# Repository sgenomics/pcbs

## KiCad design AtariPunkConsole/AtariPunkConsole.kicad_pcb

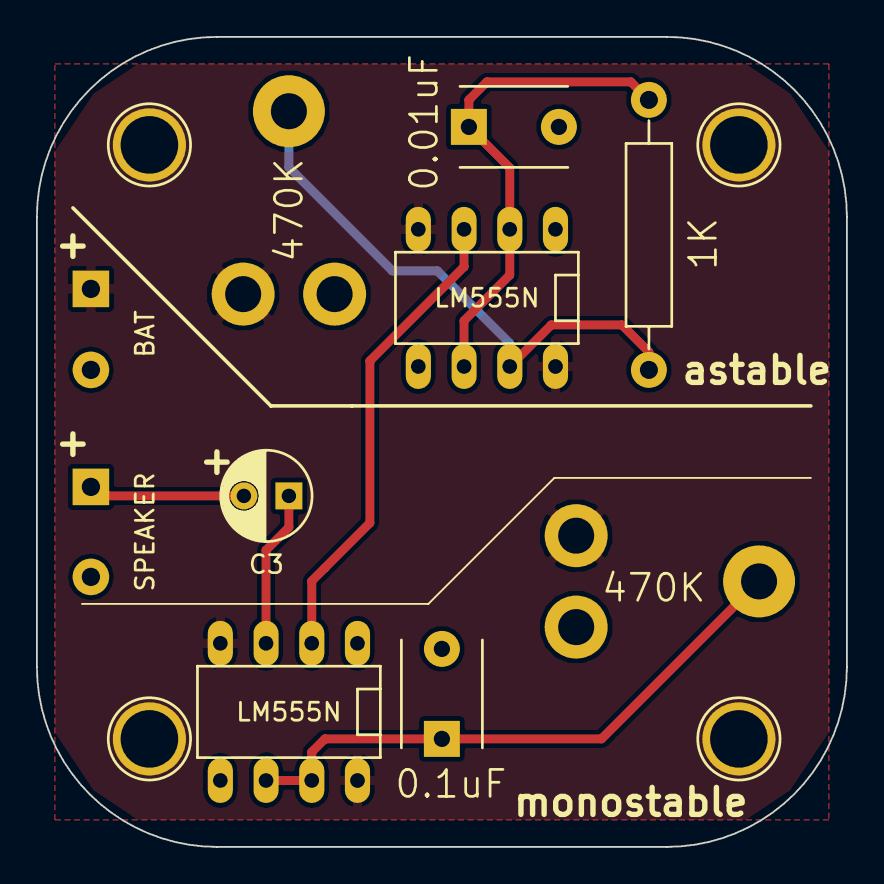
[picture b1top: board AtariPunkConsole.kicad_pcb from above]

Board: 2 copper layers, 45.0 x 45.0 mm, 10 parts (0 on the bottom side), 8 nets.

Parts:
C1: 0.01uF; C_Disc_D6_P5
C2: 0.1uF; C_Disc_D6_P5
C3: 10uF; C_Radial_D5_L11_P2.5
P1: SPEAKER; Socket_Strip_Straight_1x02
P2: BAT; Socket_Strip_Straight_1x02
R1: 1K; Resistor_Horizontal_RM15mm
U1, U2: LM555N; DIP-8__300
VR1, VR2: 470K; PNZ10Z

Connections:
+9V: P2.1, U1.4, U1.8, U2.4, U2.8, VR1.1, VR2.1
GND: C1.2, C2.2, P1.2, P2.2, U1.1, U2.1
unnamed: C1.1, R1.2, U1.2, U1.6
unnamed: C2.1, U2.6, U2.7, VR2.2
unnamed: C3.1, U2.3
unnamed: C3.2, P1.1
unnamed: R1.1, U1.7, VR1.2
unnamed: U1.3, U2.2

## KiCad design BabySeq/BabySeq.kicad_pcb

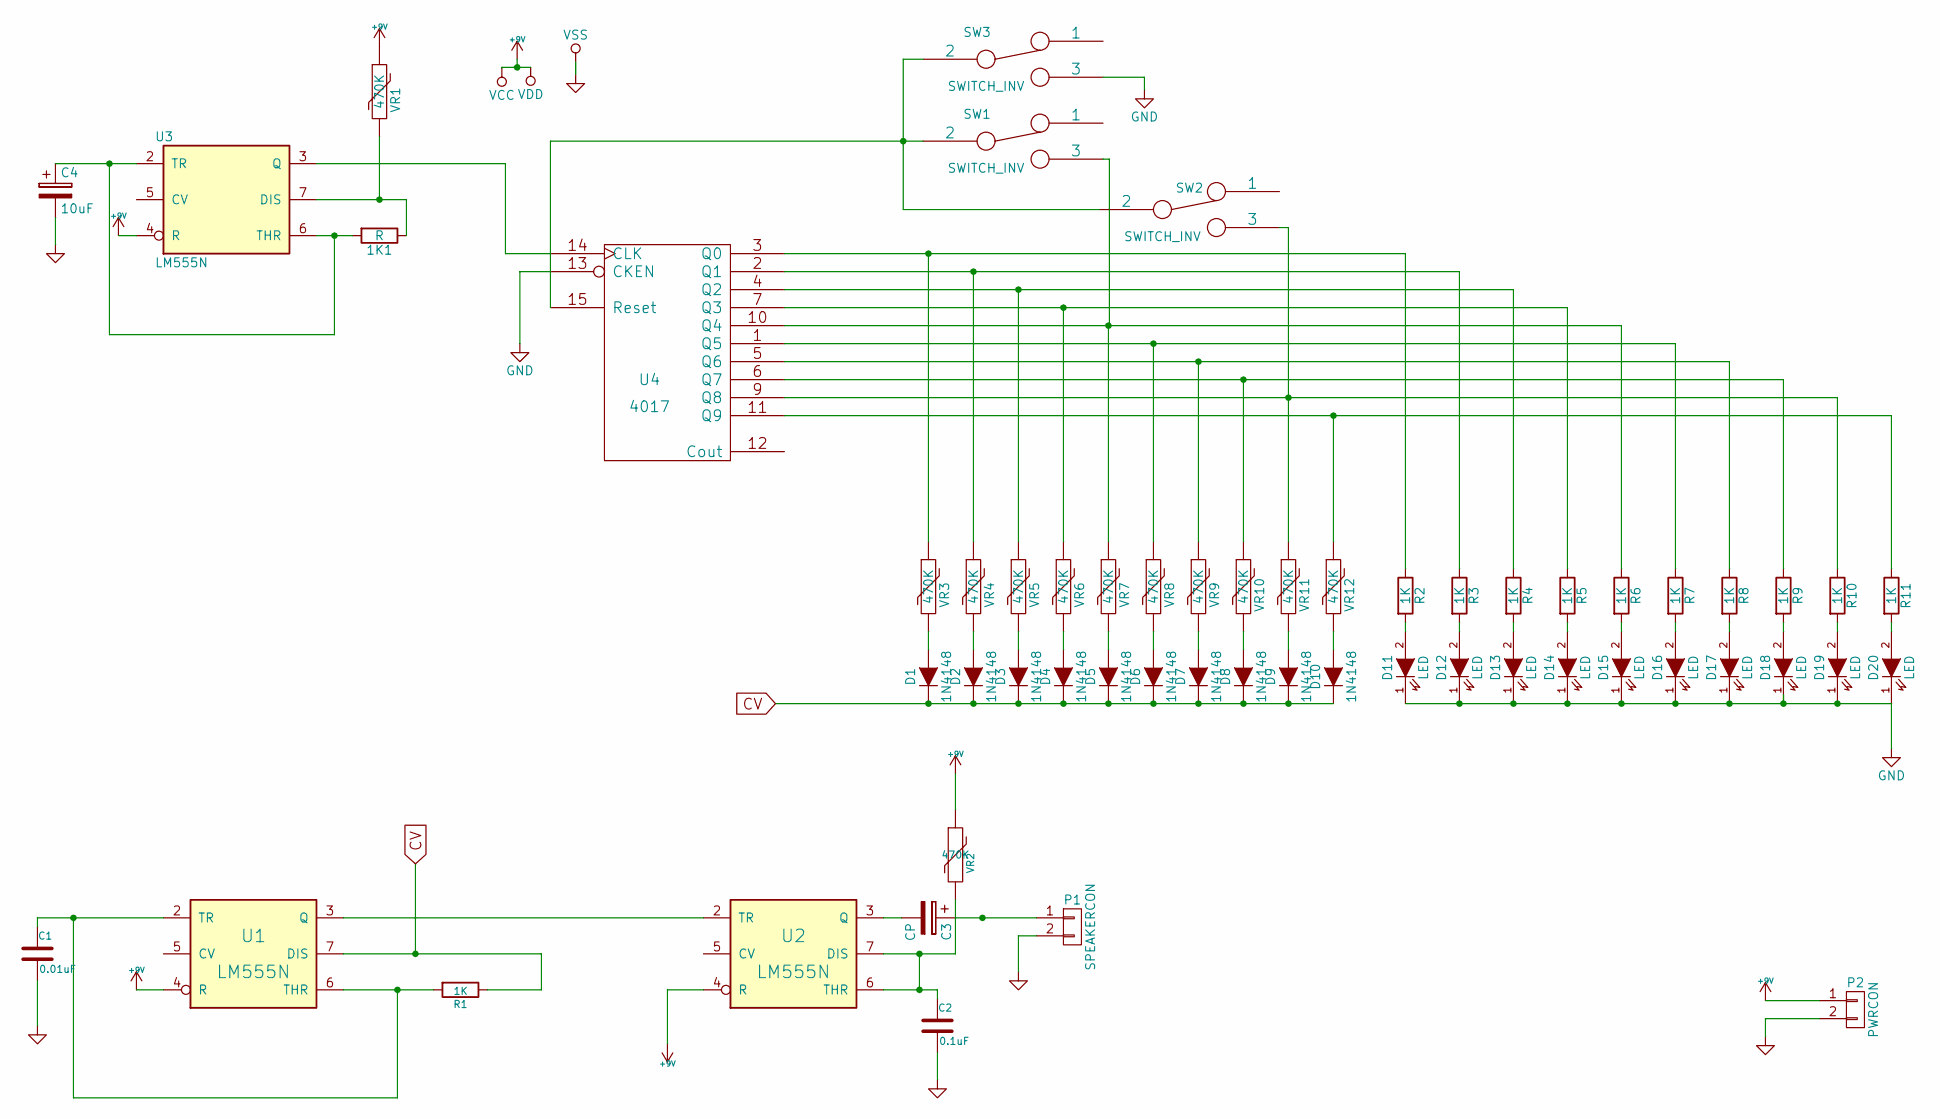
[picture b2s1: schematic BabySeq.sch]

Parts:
1K1: R; Resistor_Horizontal_RM15mm
C1: 0.01uF; C_Disc_D6_P5
C2: 0.1uF; C_Disc_D6_P5
C3: CP; C_Radial_D5_L11_P2.5
C4: 10uF; C_Radial_D5_L11_P2.5
D1, D2, D3, D4, D5, D6, D7, D8, D9, D10: 1N4148; Diode_DO-35_SOD27_Horizontal_RM10
D11, D12, D13, D14, D15, D16, D17, D18, D19, D20: LED; LED-5MM
P1: SPEAKERCON; Socket_Strip_Straight_1x02
P2: PWRCON; Socket_Strip_Straight_1x02
R1, R2, R3, R4, R5, R6, R7, R8, R9, R10, R11: 1K; Resistor_Horizontal_RM10mm
SW1, SW2, SW3: SWITCH_INV; CK_FARN1201430
U1, U2, U3: LM555N; DIP-8_W7.62mm_LongPads
U4: 4017; DIP-16_W7.62mm_LongPads
VR1, VR2, VR3, VR4, VR5, VR6, VR7, VR8, VR9, VR10, VR11, VR12: 470K; PNZ10Z

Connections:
+9V: P2.1, U1.4 (R), U1.8 (VCC), U2.4 (R), U2.8 (VCC), U3.4 (R), U3.8 (VCC), U4.16 (VDD), VR1.1, VR2.1
CV: D1.1 (K), D2.1 (K), D3.1 (K), D4.1 (K), D5.1 (K), D6.1 (K), D7.1 (K), D8.1 (K), D9.1 (K), D10.1 (K), R1.1, U1.7 (DIS)
GND: C1.2, C2.2, C4.2, D11.1 (K), D12.1 (K), D13.1 (K), D14.1 (K), D15.1 (K), D16.1 (K), D17.1 (K), D18.1 (K), D19.1 (K), D20.1 (K), P1.2, P2.2, SW3.3, U1.1 (GND), U2.1 (GND), U3.1 (GND), U4.8 (VSS), U4.13 (CKEN)
unnamed: 1K1.1, U3.7 (DIS), VR1.2
unnamed: 1K1.2, C4.1, U3.2 (TR), U3.6 (THR)
unnamed: C1.1, R1.2, U1.2 (TR), U1.6 (THR)
unnamed: C2.1, U2.6 (THR), U2.7 (DIS), VR2.2
unnamed: C3.1, P1.1
unnamed: C3.2, U2.3 (Q)
unnamed: D1.2 (A), VR3.2
unnamed: D2.2 (A), VR4.2
unnamed: D3.2 (A), VR5.2
unnamed: D4.2 (A), VR6.2
unnamed: D5.2 (A), VR7.2
unnamed: D6.2 (A), VR8.2
unnamed: D7.2 (A), VR9.2
unnamed: D8.2 (A), VR10.2
unnamed: D9.2 (A), VR11.2
unnamed: D10.2 (A), VR12.2
unnamed: D11.2 (A), R2.2
unnamed: D12.2 (A), R3.2
unnamed: D13.2 (A), R4.2
unnamed: D14.2 (A), R5.2
unnamed: D15.2 (A), R6.2
unnamed: D16.2 (A), R7.2
unnamed: D17.2 (A), R8.2
unnamed: D18.2 (A), R9.2
unnamed: D19.2 (A), R10.2
unnamed: D20.2 (A), R11.2
unnamed: R2.1, U4.3 (Q0), VR3.1
unnamed: R3.1, U4.2 (Q1), VR4.1
unnamed: R4.1, U4.4 (Q2), VR5.1
unnamed: R5.1, U4.7 (Q3), VR6.1
unnamed: R6.1, SW1.3, U4.10 (Q4), VR7.1
unnamed: R7.1, U4.1 (Q5), VR8.1
unnamed: R8.1, U4.5 (Q6), VR9.1
unnamed: R9.1, U4.6 (Q7), VR10.1
unnamed: R10.1, SW2.3, U4.9 (Q8), VR11.1
unnamed: R11.1, U4.11 (Q9), VR12.1
unnamed: SW1.2, SW2.2, SW3.2, U4.15 (Reset)
unnamed: U1.3 (Q), U2.2 (TR)
unnamed: U3.3 (Q), U4.14 (CLK)

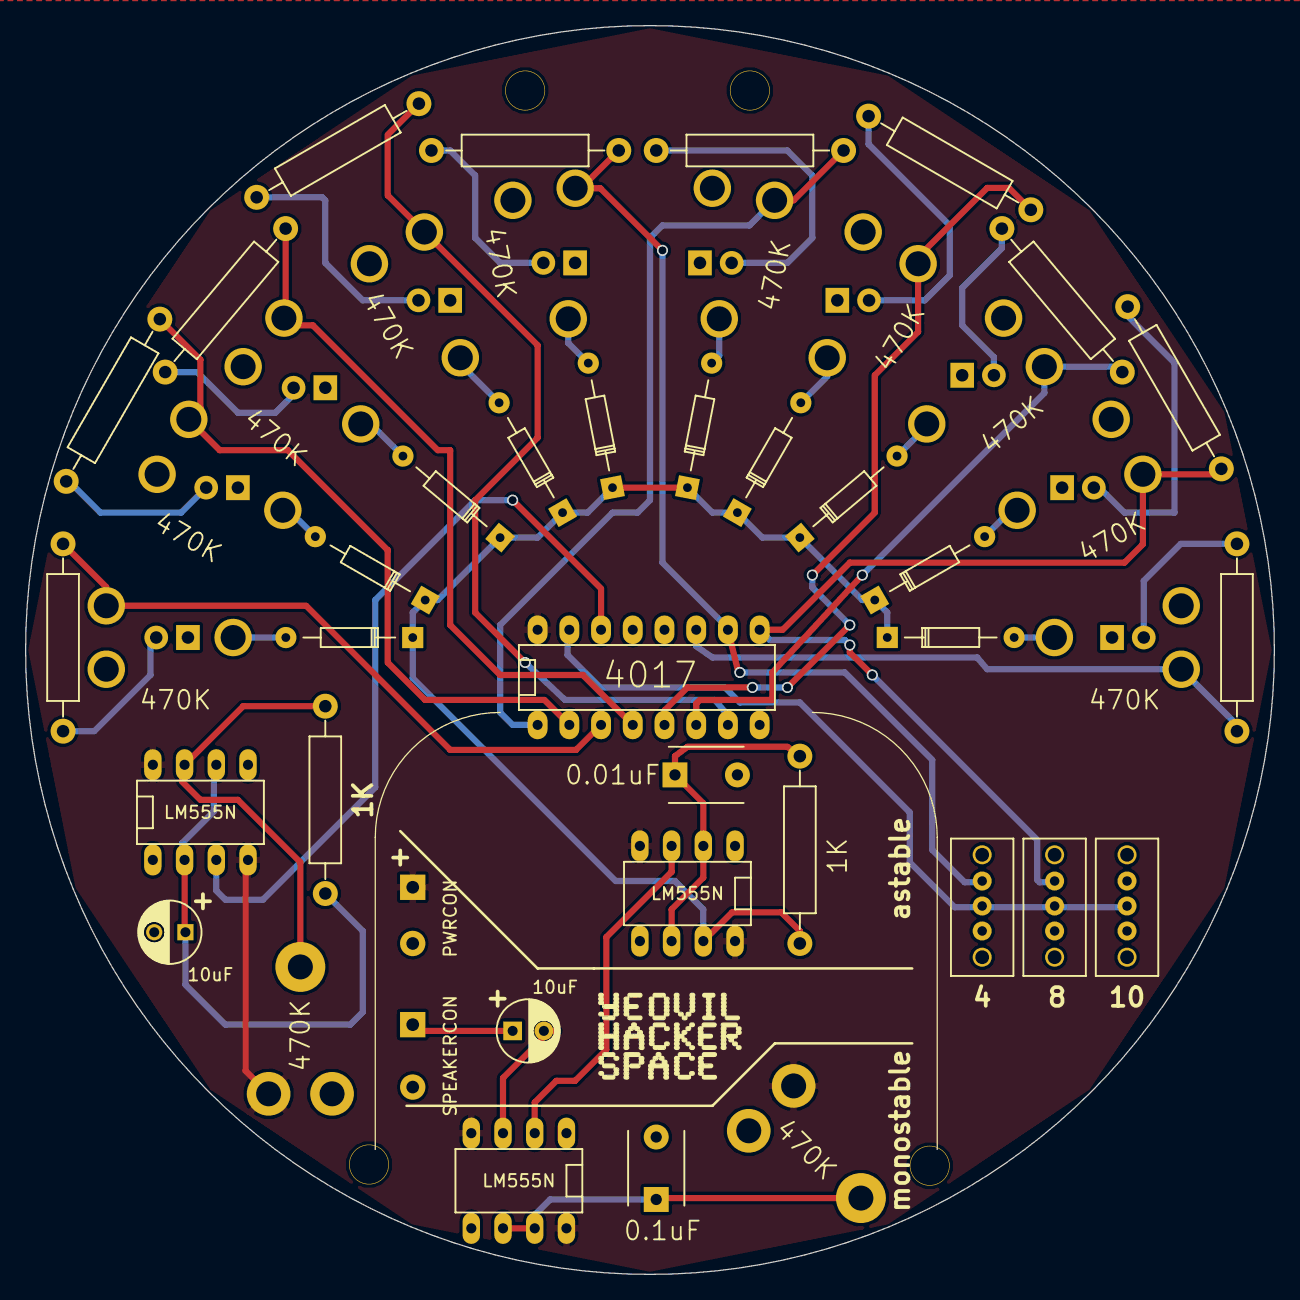
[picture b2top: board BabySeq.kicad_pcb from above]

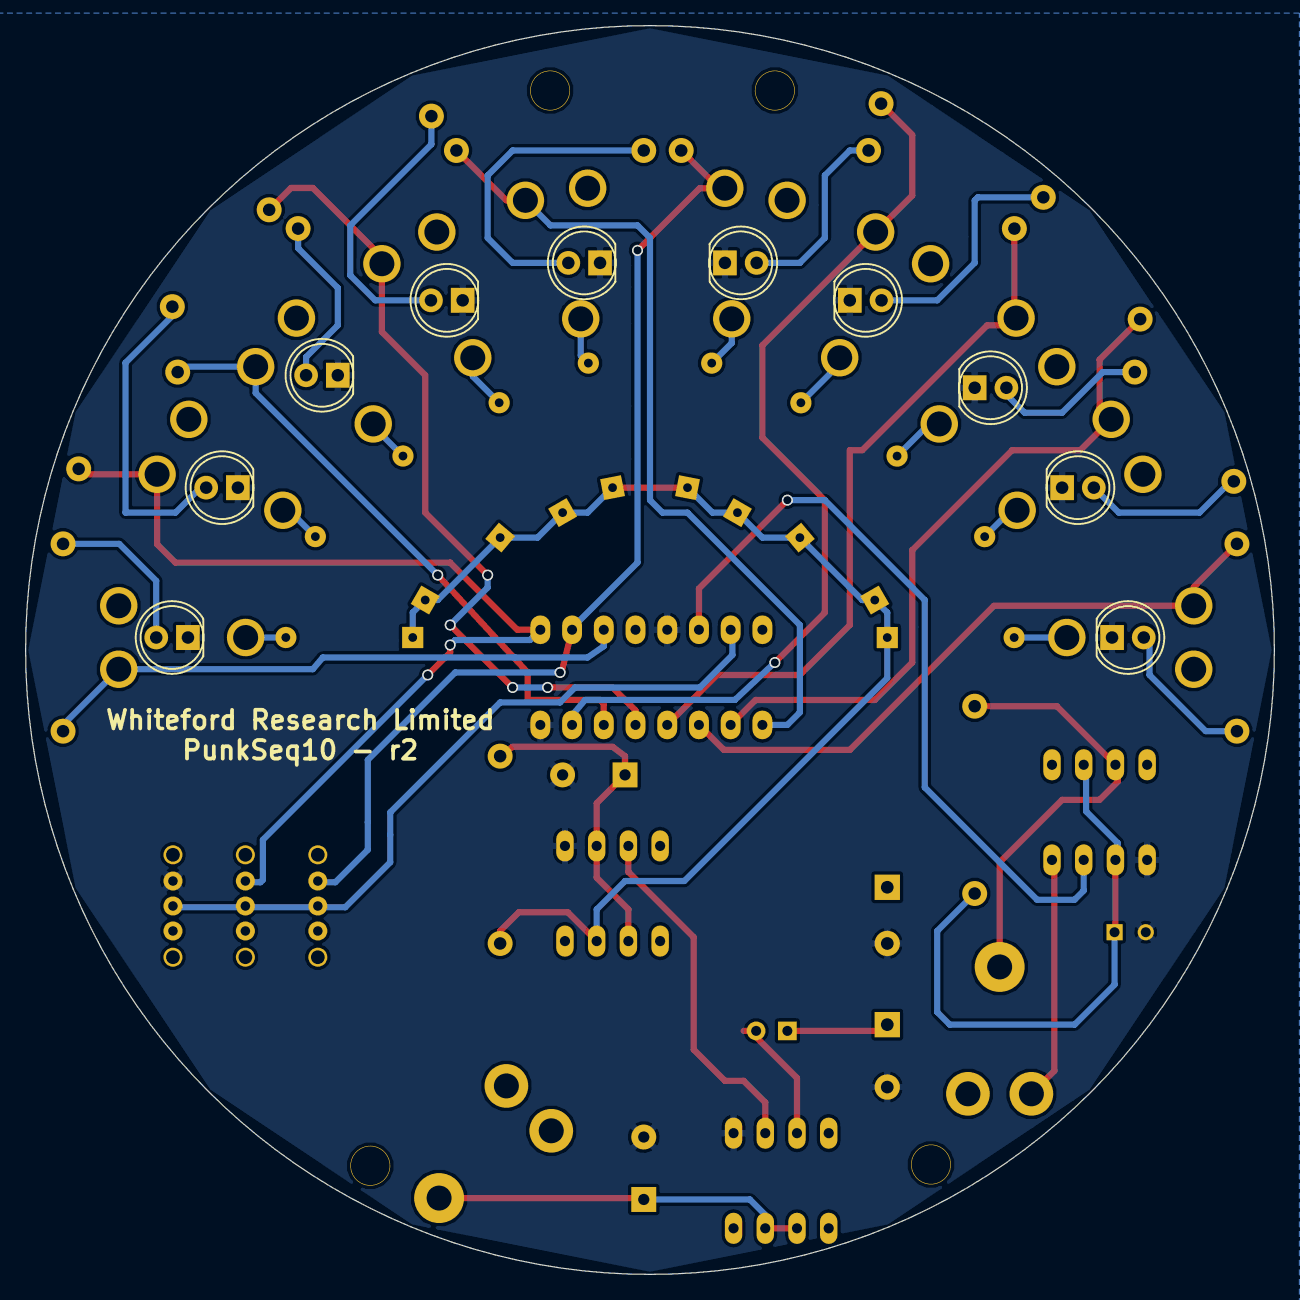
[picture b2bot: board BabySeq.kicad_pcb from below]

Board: 2 copper layers, 100.0 x 100.0 mm, 57 parts (10 on the bottom side), 42 nets.

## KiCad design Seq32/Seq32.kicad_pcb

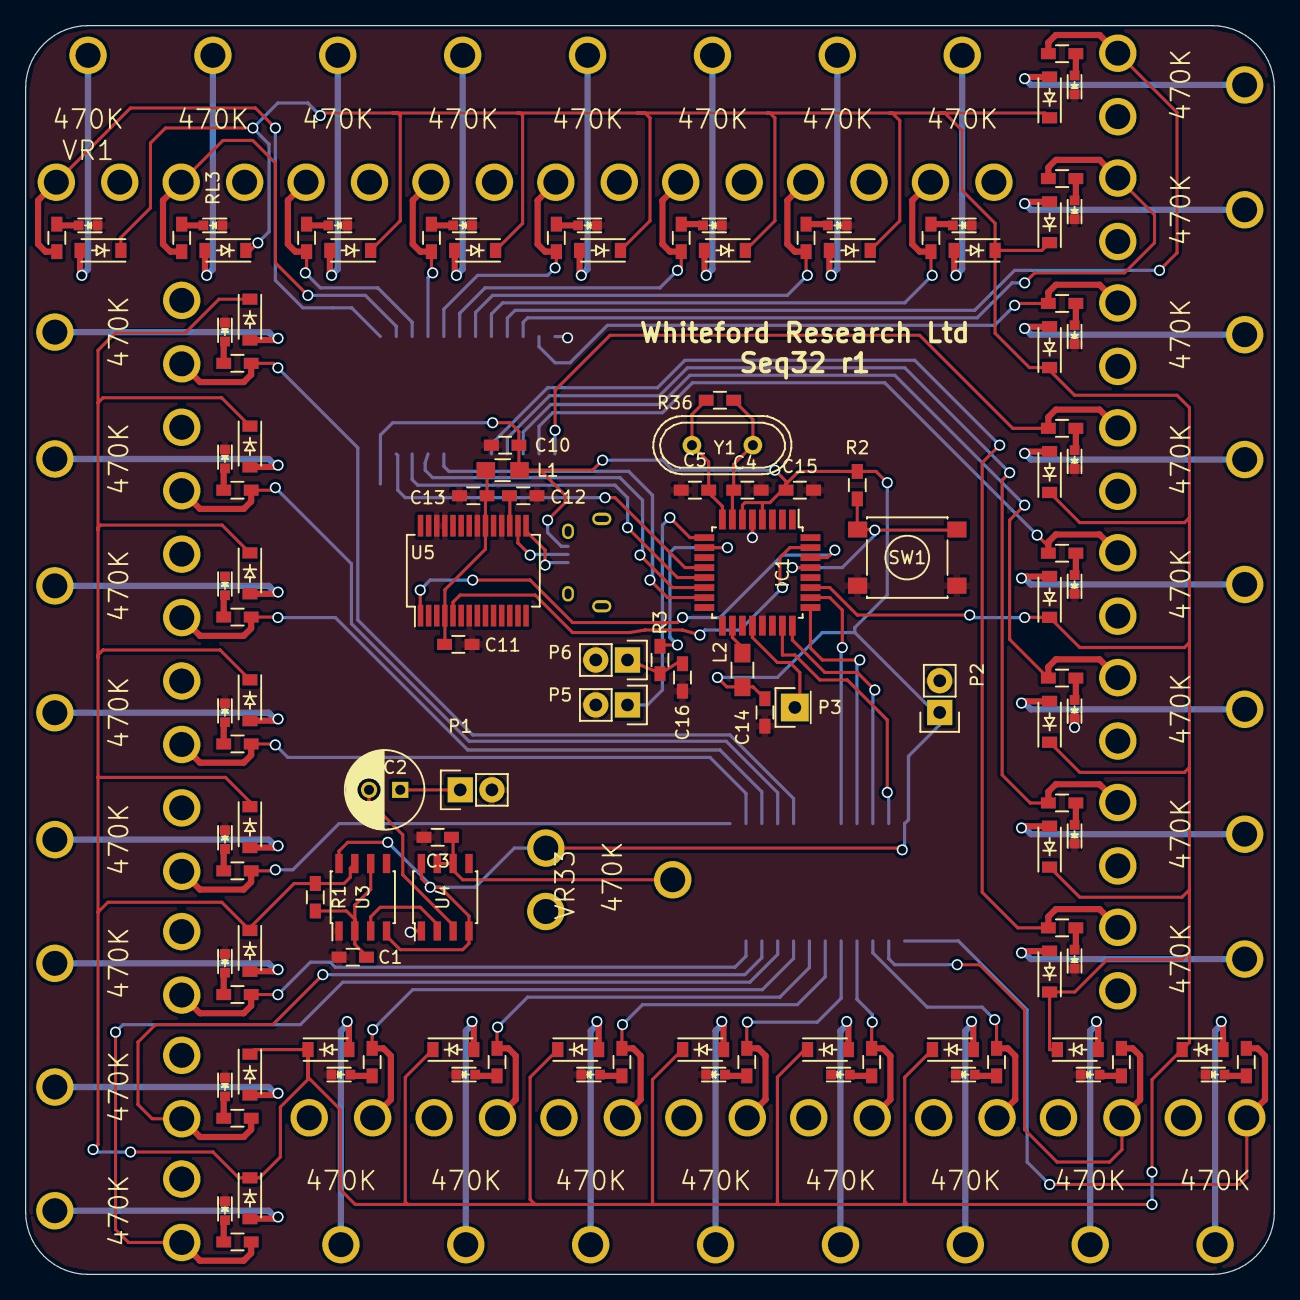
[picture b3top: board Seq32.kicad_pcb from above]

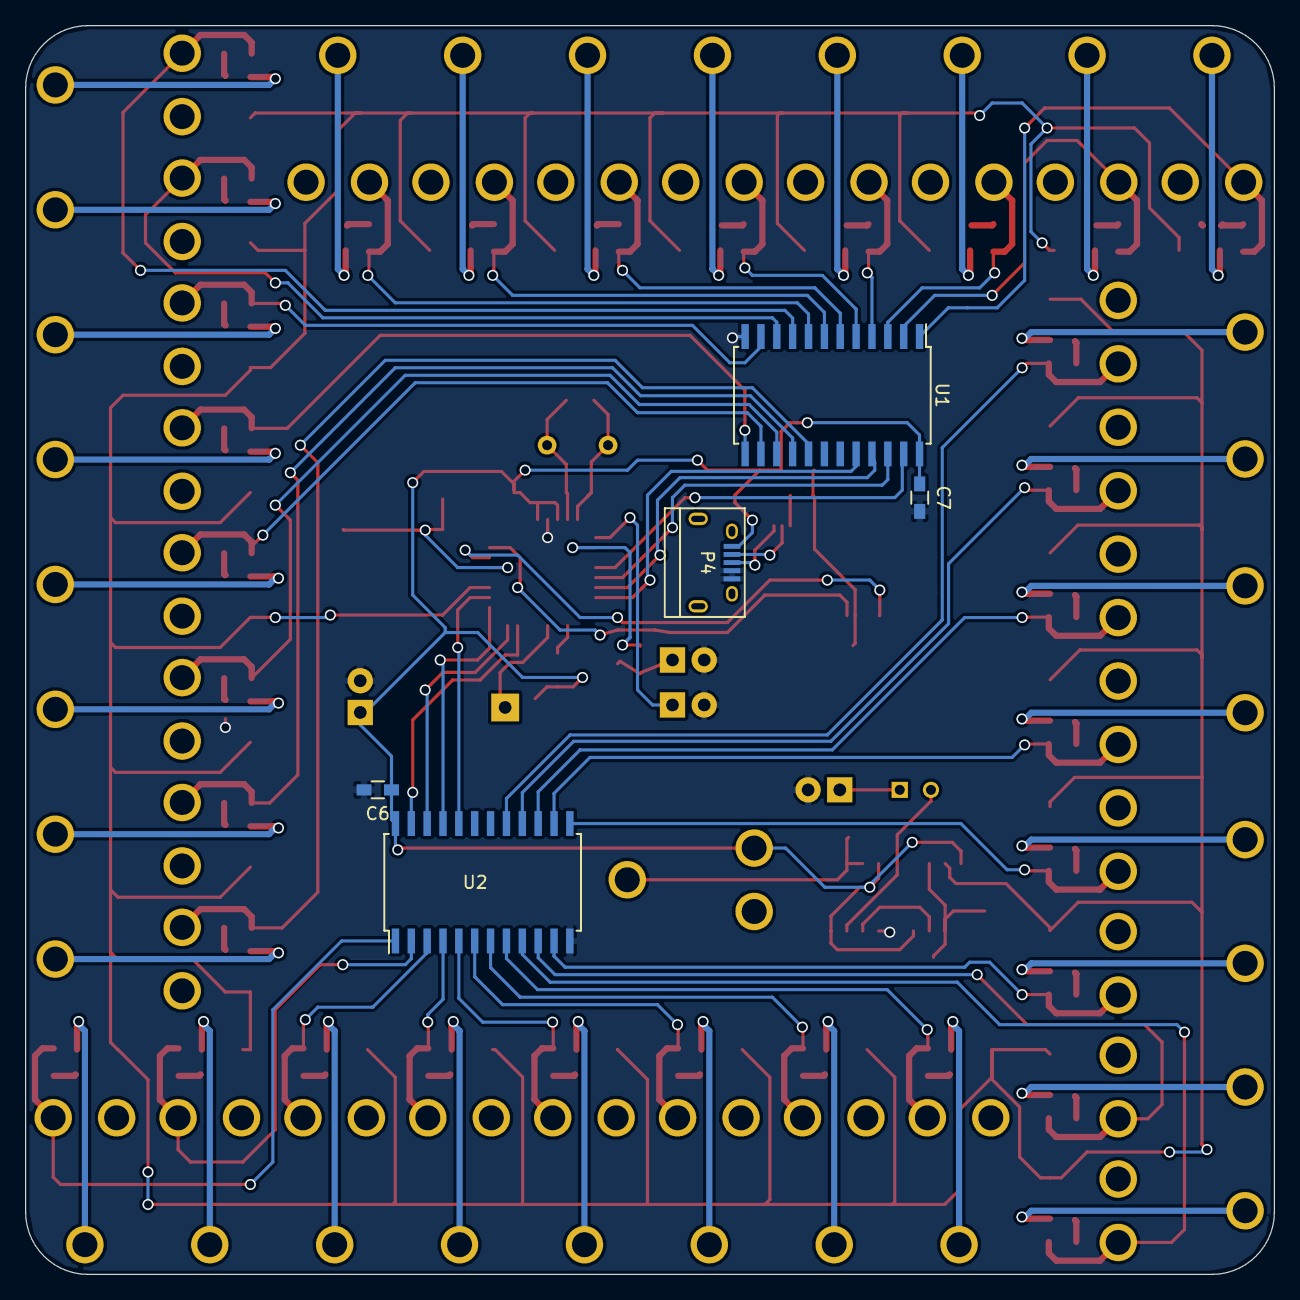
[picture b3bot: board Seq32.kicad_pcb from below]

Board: 2 copper layers, 100.0 x 100.0 mm, 163 parts (5 on the bottom side), 126 nets.

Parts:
C1: 0.01uF; R_0603_HandSoldering
C2: CP; C_Radial_D6.3_L11.2_P2.5
C3, C6, C7, C11, C13, C15: 0.1uF; R_0603_HandSoldering
C4, C5: 22pF; R_0603_HandSoldering
C10: 10nF; R_0603_HandSoldering
C12: 100nF; R_0603_HandSoldering
C14: 1uF; R_0603_HandSoldering
C16: C_Small; R_0603_HandSoldering
D1, D2, D3, D4, D5, D6, D7, D8, D9, D10, D11, D12, D13, D14, D15, D16, D17, D18, D19, D20, D21, D22, D23, D24, D25, D26, D27, D28, D29, D30, D31, D32: 1N4148; SOD-123
IC1: ATMEGA328-A; TQFP-32_7x7mm_Pitch0.8mm
L1: bead 0805; R_0805_HandSoldering
L2: uH; R_0805_HandSoldering
LED1, LED2, LED3, LED4, LED5, LED6, LED7, LED8, LED9, LED10, LED11, LED12, LED13, LED14, LED15, LED16, LED17, LED18, LED19, LED20, LED21, LED22, LED23, LED24, LED25, LED26, LED27, LED28, LED29, LED30, LED31, LED32: LED; LED_0603
P1: SPEAKERCON; Socket_Strip_Straight_1x02
P2: PWR; Socket_Strip_Straight_1x02
P3: AREF; Socket_Strip_Straight_1x01
P4: USB_A; USB_Micro-B
P5: GATE; Socket_Strip_Straight_1x02
P6: CV; Socket_Strip_Straight_1x02
R1: 1K; R_0603_HandSoldering
R2: 10K; R_0603_HandSoldering
R3: R; R_0603_HandSoldering
R36: 0; R_0603_HandSoldering
RL1, RL2, RL3, RL4, RL5, RL6, RL7, RL8, RL9, RL10, RL11, RL12, RL13, RL14, RL15, RL16, RL17, RL18, RL19, RL20, RL21, RL22, RL23, RL24, RL25, RL26, RL27, RL28, RL29, RL30, RL31, RL32: R; R_0603_HandSoldering
SW1: SW_PUSH; SW_SPST_PTS645
U1, U2: 74LS154; SOIC-24_7.5x15.4mm_Pitch1.27mm
U3, U4: LM555N; SOIC-8_3.9x4.9mm_Pitch1.27mm
U5: FT232; SSOP-28_5.3x10.2mm_Pitch0.65mm
VR1, VR2, VR3, VR4, VR5, VR6, VR7, VR8, VR9, VR10, VR11, VR12, VR13, VR14, VR15, VR16, VR17, VR18, VR19, VR20, VR21, VR22, VR23, VR24, VR25, VR26, VR27, VR28, VR29, VR30, VR31, VR32, VR33: 470K; PNZ10Z
Y1: Crystal; Crystal_HC49-U_Vertical

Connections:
+5V: C6.1, C7.1, C10.1, C14.1, C15.1, IC1.4, IC1.6, L1.1, L2.1, P2.1, P4.1, R2.1, U1.24, U2.24, U3.4, U3.8, U4.4, U4.8, VR33.1
CV: D1.1, D2.1, D3.1, D4.1, D5.1, D6.1, D7.1, D8.1, D9.1, D10.1, D11.1, D12.1, D13.1, D14.1, D15.1, D16.1, D17.1, D18.1, D19.1, D20.1, D21.1, D22.1, D23.1, D24.1, D25.1, D26.1, D27.1, D28.1, D29.1, D30.1, D31.1, D32.1, IC1.27, R1.1, U3.7
FT232_RX: IC1.31, U5.5
FT232_TX: IC1.30, U5.1
GND: C1.2, C3.2, C4.1, C5.1, C6.2, C7.2, C10.2, C11.1, C12.2, C13.1, C14.2, C15.2, C16.2, IC1.3, IC1.5, IC1.21, LED1.1, LED2.1, LED3.1, LED4.1, LED5.1, LED6.1, LED7.1, LED8.1, LED9.1, LED10.1, LED11.1, LED12.1, LED13.1, LED14.1, LED15.1, LED16.1, LED17.1, LED18.1, LED19.1, LED21.1, LED22.1, LED23.1, LED24.1, LED25.1, LED26.1, LED27.1, LED28.1, LED29.1, LED31.1, LED32.1, P1.2, P2.2, P4.4, P4.5, P5.2, P6.2, SW1.2, U1.12, U2.12, U3.1, U4.1, U5.7, U5.18, U5.21, U5.25, U5.26
M1: RL1.1, U1.1, VR1.1
M2: RL2.1, U1.2, VR2.1
M3: RL3.1, U1.3, VR3.1
M4: RL4.1, U1.4, VR4.1
M5: RL5.1, U1.5, VR5.1
M6: RL6.1, U1.6, VR6.1
M7: RL7.1, U1.7, VR7.1
M8: RL8.1, U1.8, VR8.1
M9: RL9.1, U1.9, VR9.1
M10: RL10.1, U1.10, VR10.1
M11: RL11.1, U1.11, VR11.1
M12: RL12.1, U1.13, VR12.1
M13: RL13.1, U1.14, VR13.1
M14: RL14.1, U1.15, VR14.1
M15: RL15.1, U1.16, VR15.1
M16: RL16.1, U1.17, VR16.1
M17: RL17.1, U2.1, VR17.1
M18: RL18.1, U2.2, VR18.1
M19: RL19.1, U2.3, VR19.1
M20: RL20.1, U2.4, VR20.1
M21: RL21.1, U2.5, VR21.1
M22: RL22.1, U2.6, VR22.1
M23: RL23.1, U2.7, VR23.1
M24: RL24.1, U2.8, VR24.1
M25: RL25.1, U2.9, VR25.1
M26: RL26.1, U2.10, VR26.1
M27: RL27.1, U2.11, VR27.1
M28: RL28.1, U2.13, VR28.1
M29: RL29.1, U2.14, VR29.1
M30: RL30.1, U2.15, VR30.1
M31: RL31.1, U2.16, VR31.1
M32: RL32.1, U2.17, VR32.1
MUX1_1: IC1.12, U1.23
MUX1_2: IC1.13, U1.22
MUX1_3: IC1.14, U1.21
MUX1_4: IC1.15, U1.20
MUX2_1: IC1.23, U2.23
MUX2_2: IC1.24, U2.22
MUX2_3: IC1.25, U2.21
MUX2_4: IC1.26, U2.20
unnamed: C1.1, R1.2, U3.2, U3.6
unnamed: C2.1, P1.1
unnamed: C2.2, U4.3
unnamed: C3.1, U4.6, U4.7, VR33.2
unnamed: C4.2, IC1.7, R36.1, Y1.1
unnamed: C5.2, IC1.8, R36.2, Y1.2
unnamed: C11.2, C13.2, L1.2, U5.4, U5.20
unnamed: C12.1, U5.17
unnamed: C16.1, P6.1, R3.1
unnamed: D1.2, VR1.2
unnamed: D2.2, VR2.2
unnamed: D3.2, VR3.2
unnamed: D4.2, VR4.2
unnamed: D5.2, VR5.2
unnamed: D6.2, VR6.2
unnamed: D7.2, VR7.2
unnamed: D8.2, VR8.2
unnamed: D9.2, VR9.2
unnamed: D10.2, VR10.2
unnamed: D11.2, VR11.2
unnamed: D12.2, VR12.2
unnamed: D13.2, VR13.2
unnamed: D14.2, VR14.2
unnamed: D15.2, VR15.2
unnamed: D16.2, VR16.2
unnamed: D17.2, VR17.2
unnamed: D18.2, VR18.2
unnamed: D19.2, VR19.2
unnamed: D20.2, VR20.2
unnamed: D21.2, VR21.2
unnamed: D22.2, VR22.2
unnamed: D23.2, VR23.2
unnamed: D24.2, VR24.2
unnamed: D25.2, VR25.2
unnamed: D26.2, VR26.2
unnamed: D27.2, VR27.2
unnamed: D28.2, VR28.2
unnamed: D29.2, VR29.2
unnamed: D30.2, VR30.2
unnamed: D31.2, VR31.2
unnamed: D32.2, VR32.2
unnamed: IC1.9, P5.1
unnamed: IC1.10, R3.2
unnamed: IC1.18, L2.2
unnamed: IC1.20, P3.1
unnamed: IC1.29, R2.2, SW1.1
unnamed: LED1.2, RL1.2
unnamed: LED2.2, RL2.2
unnamed: LED3.2, RL3.2
unnamed: LED4.2, RL4.2
unnamed: LED5.2, RL5.2
unnamed: LED6.2, RL6.2
unnamed: LED7.2, RL7.2
unnamed: LED8.2, RL8.2
unnamed: LED9.2, RL9.2
unnamed: LED10.2, RL10.2
unnamed: LED11.2, RL11.2
unnamed: LED12.2, RL12.2
unnamed: LED13.2, RL13.2
unnamed: LED14.2, RL14.2
unnamed: LED15.2, RL15.2
unnamed: LED16.2, RL16.2
unnamed: LED17.2, RL17.2
unnamed: LED18.2, RL18.2
unnamed: LED19.2, RL19.2
unnamed: LED20.2, RL20.2
unnamed: LED21.2, RL21.2
unnamed: LED22.2, RL22.2
unnamed: LED23.2, RL23.2
unnamed: LED24.2, RL24.2
unnamed: LED25.2, RL25.2
unnamed: LED26.2, RL26.2
unnamed: LED27.2, RL27.2
unnamed: LED28.2, RL28.2
unnamed: LED29.2, RL29.2
unnamed: LED30.2, RL30.2
unnamed: LED31.2, RL31.2
unnamed: LED32.2, RL32.2
unnamed: U3.3, U4.2
USB_DM: P4.2, U5.16
USB_DP: P4.3, U5.15

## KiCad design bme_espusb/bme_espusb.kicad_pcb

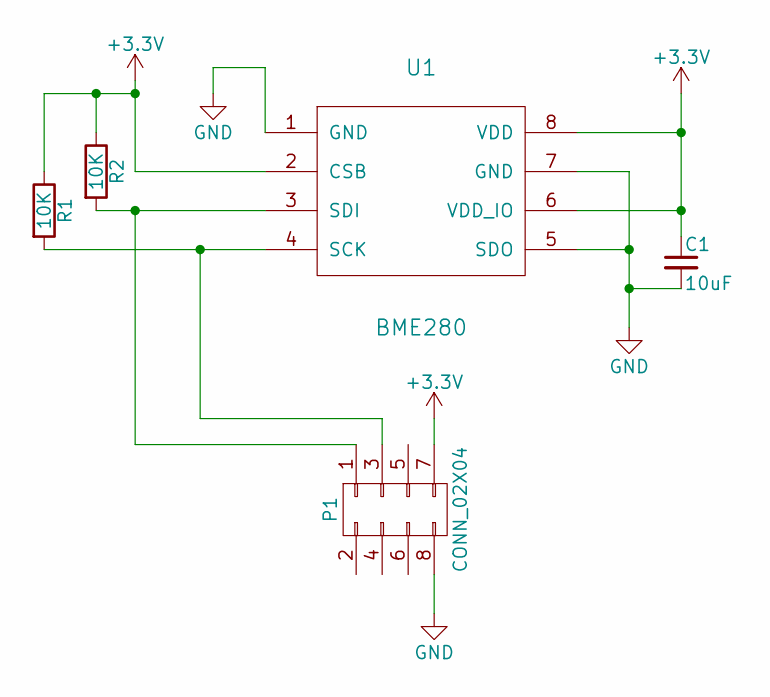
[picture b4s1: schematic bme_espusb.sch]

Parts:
C1: 10uF; C_0805_HandSoldering
P1: CONN_02X04; Socket_Strip_Straight_2x04
R1, R2: 10K; R_0603_HandSoldering
U1: BME280

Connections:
+3V3: C1.1, P1.7, R1.1, R2.1, U1.2 (CSB), U1.6 (VDD_IO), U1.8 (VDD)
GND: C1.2, P1.8, U1.1 (GND), U1.5 (SDO), U1.7 (GND)
unnamed: P1.1, R2.2, U1.3 (SDI)
unnamed: P1.3, R1.2, U1.4 (SCK)

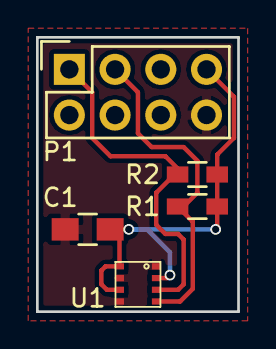
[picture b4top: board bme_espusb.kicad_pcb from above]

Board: 2 copper layers, 11.2 x 15.2 mm, 5 parts (0 on the bottom side), 4 nets.

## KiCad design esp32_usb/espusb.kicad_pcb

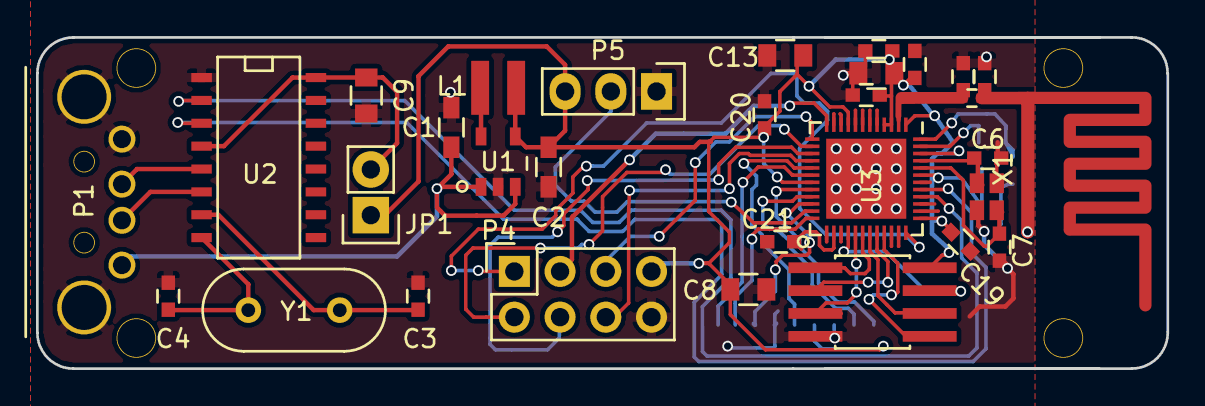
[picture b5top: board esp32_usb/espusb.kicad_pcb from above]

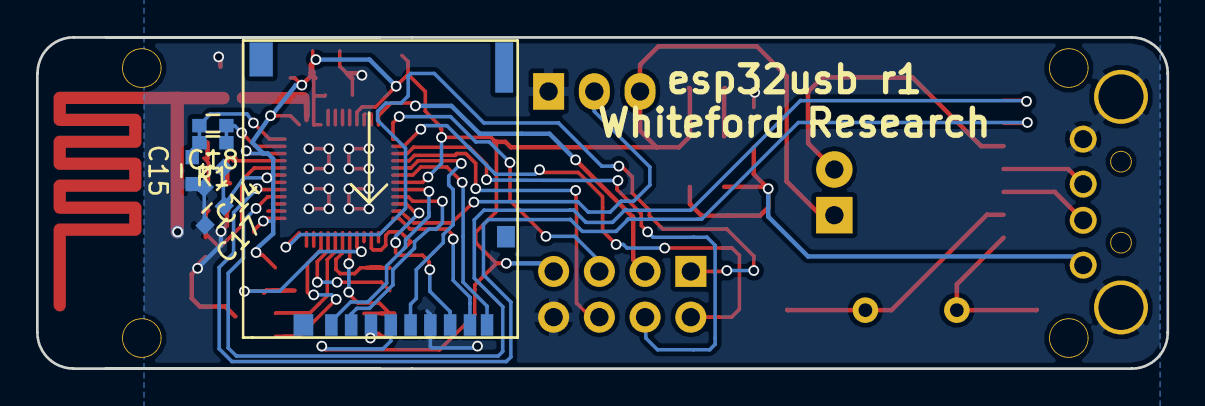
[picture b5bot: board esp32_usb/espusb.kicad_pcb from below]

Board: 2 copper layers, 62.8 x 18.4 mm, 51 parts (6 on the bottom side), 50 nets.

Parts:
C1, C2: 4.7uF; R_0603_HandSoldering
C3, C4: 22pF; C_0603
C5: 5.6pF; C_0402
C6, C7: ?; C_0603
C8, C11, C13: 10uF; C_0805
C9: 100nF; C_0805
C10, C17, C21: 1uF; C_0603
C12: C_Small; C_0603
C14: 100pF; C_0603
C15: 10nF; C_0603
C16, C19, C20: 0.1uF; C_0603
C18: 3nF; C_0603
CON1: SD_Card; MICROSD
JP1: JUMPER; Socket_Strip_Straight_1x02
L1: 4.7uH; TDK_VLS_INDUCTOR
L3, L4: INDUCTOR; C_0603
P1: USB_A
P4: CONN_02X04; Socket_Strip_Straight_2x04
P5: CONN_01X03; Socket_Strip_Straight_1x03
R1: 20K; C_0603
U1: MCP1603; TSOT-5
U2: ch340; SO-16-N
U3: ESP32; UQFN-48-1EP_6x6mm_Pitch0.4mm
U4: SERFLASH; SOIC-8_3.9x4.9mm_Pitch1.27mm
W1, W2, W3, W4, W5, W6, W7, W8, W9, W10, W11, W12, W13, W14: TEST_1P; testpoint
X1: CRYSTAL_SMD; smd_xtal
Y1: 12MHz; HC-49V
svg2mod: G***; svg2mod

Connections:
32K_XN: P4.5, U3.13
32_XP: P4.3, U3.12
+3V3: C2.1, C8.1, C10.1, C11.1, C12.1, C13.1, C14.1, C16.1, C17.1, C19.1, C20.1, CON1.4, JP1.1, L1.2, P4.7, P5.3, U1.4, U3.1, U3.3, U3.4, U3.9, U3.19, U3.37, U3.43, U3.46, U4.8
+5V: C1.1, P1.1, U1.1, U1.3
FT232_RX: U2.3, U3.41
FT232_TX: U2.2, U3.40
F_CLK: U3.31, U4.6
F_CS: U3.30, U4.1
F_D0: U3.32, U4.2
F_DI: U3.33, U4.5
F_HOLD: U3.28, U4.7
F_WP: U3.29, U4.3
GND: C1.2, C2.2, C3.2, C4.2, C6.2, C7.2, C8.2, C9.2, C10.2, C11.2, C12.2, C13.2, C14.2, C15.1, C16.2, C17.2, C19.2, C20.2, C21.2, CON1.3, CON1.6, L3.2, L4.2, P1.4, P1.5, P4.8, P5.1, U1.2, U2.1, U3.49, U4.4, X1.3
GPIO0: P5.2, U3.23
GPIO23: P4.1, U3.36
GPIO25: P4.2, U3.14
GPIO26: P4.4, U3.15
GPIO27: P4.6, U3.16
HS2_CLK: CON1.5, U3.17
HS2_CMD: CON1.2, U3.21
HS2_DATA0: CON1.7, U3.22
HS2_DATA1: CON1.8, U3.24
HS2_DATA2: CON1.9, U3.18
HS2_DATA3: CON1.1, U3.20
unnamed: C5.2, L3.1
unnamed: C3.1, U2.7, Y1.1
unnamed: C4.1, U2.8, Y1.2
unnamed: C5.1, L4.1, U3.2
unnamed: C6.1, U3.45, X1.1
unnamed: C7.1, U3.44, X1.2
unnamed: C9.1, JP1.2, U2.4, U2.16
unnamed: C15.2, C18.2, R1.2, U3.48
unnamed: C18.1, R1.1, U3.47
unnamed: C21.1, U3.26, W13.1
unnamed: L1.1, U1.5
unnamed: U3.5, W3.1
unnamed: U3.6, W4.1
unnamed: U3.7, W5.1
unnamed: U3.8, W6.1
unnamed: U3.10, W1.1
unnamed: U3.11, W2.1
unnamed: U3.25, W14.1
unnamed: U3.27, W12.1
unnamed: U3.34, W11.1
unnamed: U3.35, W10.1
unnamed: U3.38, W9.1
unnamed: U3.39, W8.1
unnamed: U3.42, W7.1
USB_DM: P1.2, U2.6
USB_DP: P1.3, U2.5

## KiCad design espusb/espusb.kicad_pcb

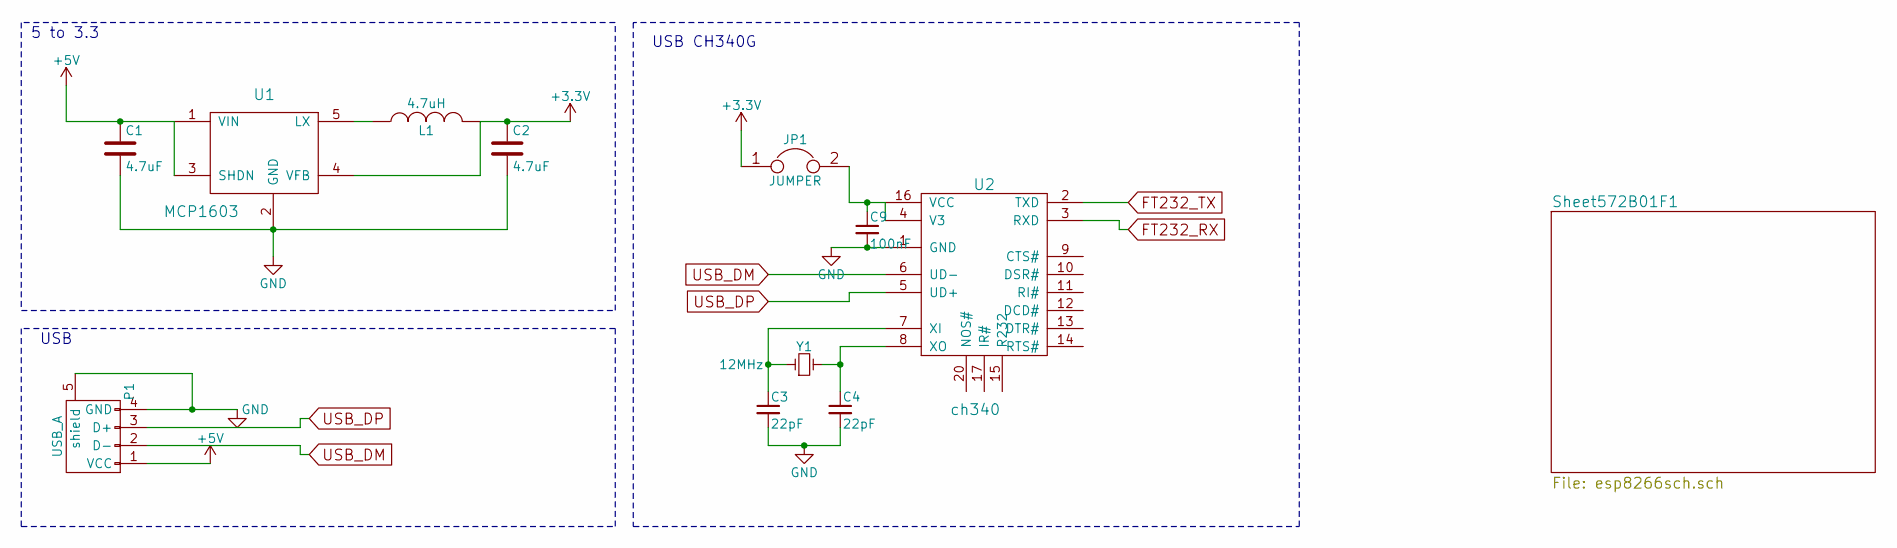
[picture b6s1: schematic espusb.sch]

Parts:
C1, C2: 4.7uF; R_0603_HandSoldering
C3, C4: 22pF; C_0603
C9: 100nF; C_0805
JP1: JUMPER; Socket_Strip_Straight_1x02
L1: 4.7uH; TDK_VLS_INDUCTOR
P1: USB_A
U1: MCP1603; TSOT-5
U2: ch340; SO-16-N
Y1: 12MHz; HC-49V

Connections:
+3V3: C2.1, JP1.1, L1.2, U1.4 (VFB); also elsewhere on the board
+5V: C1.1, P1.1 (VCC), U1.1 (VIN), U1.3 (SHDN)
FT232_RX: U2.3 (RXD); also elsewhere on the board
FT232_TX: U2.2 (TXD); also elsewhere on the board
GND: C1.2, C2.2, C3.2, C4.2, C9.2, P1.4 (GND), P1.5 (shield), U1.2 (GND), U2.1 (GND); also elsewhere on the board
unnamed: C3.1, U2.7 (XI), Y1.1
unnamed: C4.1, U2.8 (XO), Y1.2
unnamed: C9.1, JP1.2, U2.4 (V3), U2.16 (VCC)
unnamed: L1.1, U1.5 (LX)
USB_DM: P1.2 (D-), U2.6 (UD-)
USB_DP: P1.3 (D+), U2.5 (UD+)

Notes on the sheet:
5 to 3.3
USB CH340G
USB

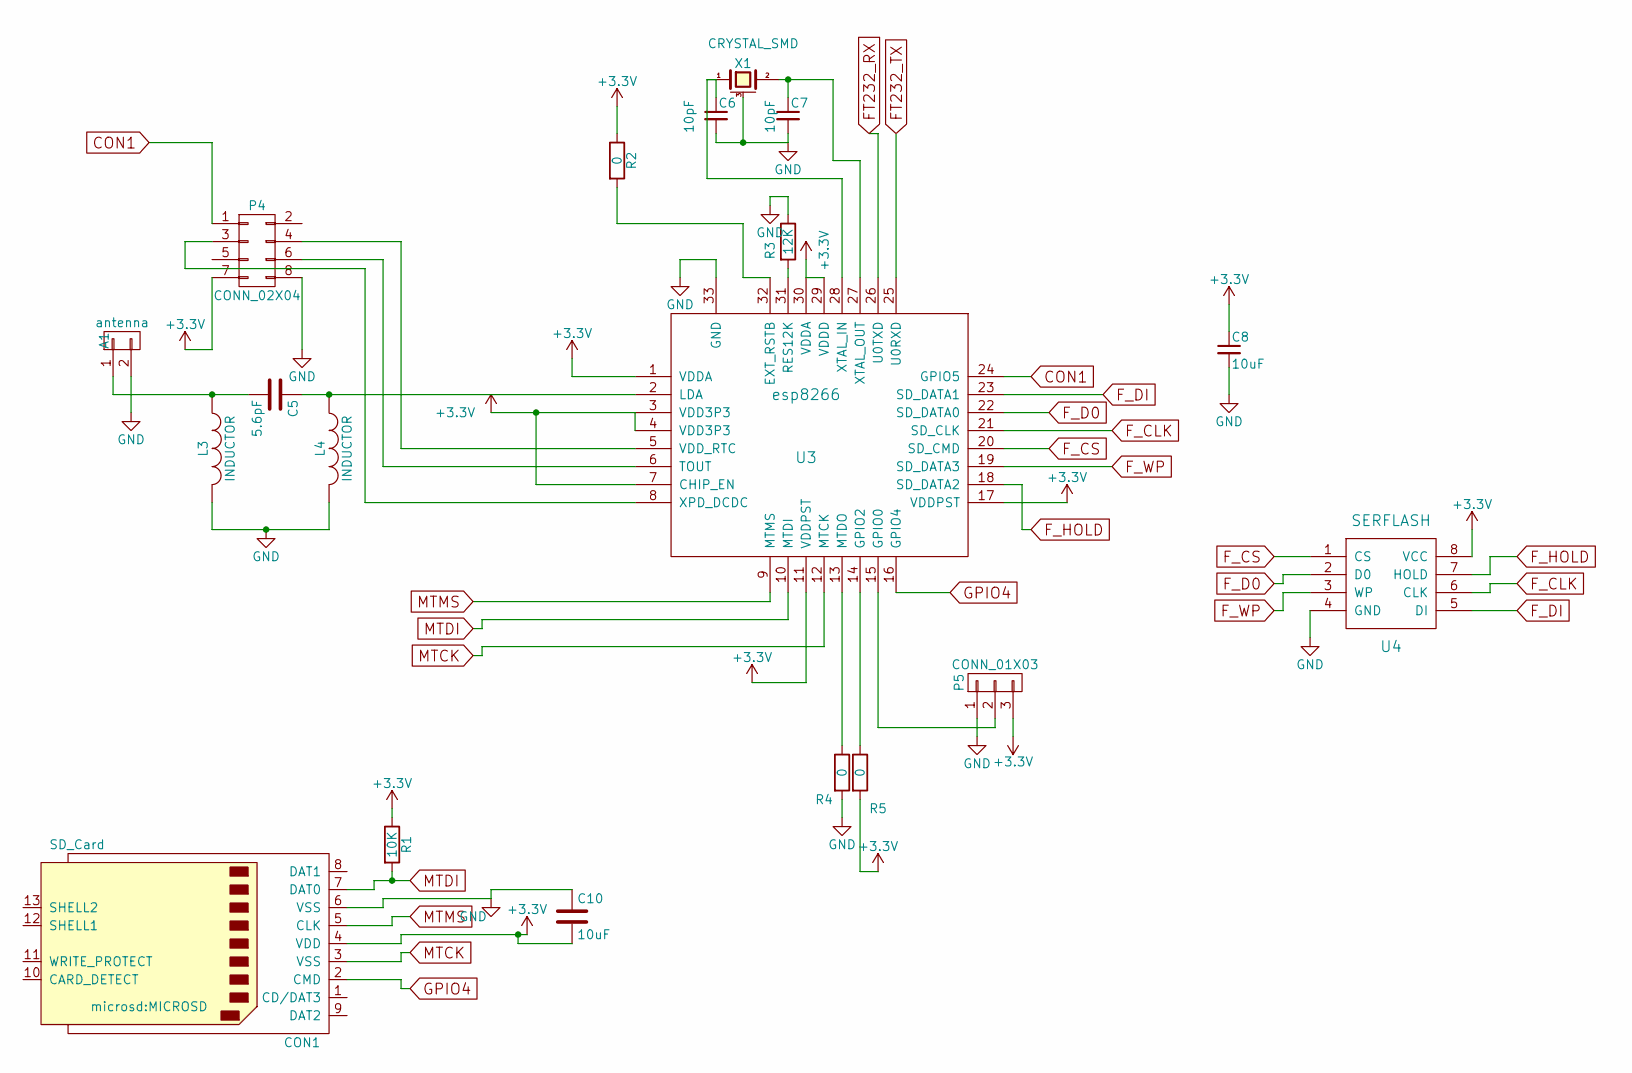
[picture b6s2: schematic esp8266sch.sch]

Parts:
A1: antenna; wifi_antenna
C5: 5.6pF; C_0402
C6, C7: 10pF; C_0402
C8, C10: 10uF; C_0805
CON1: SD_Card; MICROSD
L3, L4: INDUCTOR; C_0402
P4: CONN_02X04; Socket_Strip_Straight_2x04
P5: CONN_01X03; Socket_Strip_Straight_1x03
R1: 10K; R_0603
R2, R4, R5: 0; C_0402
R3: 12K; C_0402
U3: esp8266; QFN-32-1EP_5x5mm_Pitch0.5mm
U4: SERFLASH; SOIC-8_3.9x4.9mm_Pitch1.27mm
X1: CRYSTAL_SMD; smd_xtal

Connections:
+3V3: C8.1, C10.2, CON1.4 (VDD), P4.7, P5.3, R1.1, R2.1, R5.2, U3.1 (VDDA), U3.3 (VDD3P3), U3.4 (VDD3P3), U3.7 (CHIP_EN), U3.11 (VDDPST), U3.17 (VDDPST), U3.29 (VDDD), U3.30 (VDDA), U4.8 (VCC); also elsewhere on the board
CON1: P4.1, U3.24 (GPIO5)
FT232_RX: U3.26 (U0TXD); also elsewhere on the board
FT232_TX: U3.25 (U0RXD); also elsewhere on the board
F_CLK: U3.21 (SD_CLK), U4.6 (CLK)
F_CS: U3.20 (SD_CMD), U4.1 (CS)
F_D0: U3.22 (SD_DATA0), U4.2 (D0)
F_DI: U3.23 (SD_DATA1), U4.5 (DI)
F_HOLD: U3.18 (SD_DATA2), U4.7 (HOLD)
F_WP: U3.19 (SD_DATA3), U4.3 (WP)
GND: A1.2, C6.2, C7.2, C8.2, C10.1, CON1.6 (VSS), L3.2, L4.2, P4.8, P5.1, R3.1, R4.2, U3.33 (GND), U4.4 (GND), X1.3 (case); also elsewhere on the board
GPIO4: CON1.2 (CMD), U3.16 (GPIO4)
MTCK: CON1.3 (VSS), U3.12 (MTCK)
MTDI: CON1.7 (DAT0), R1.2, U3.10 (MTDI)
MTMS: CON1.5 (CLK), U3.9 (MTMS)
unnamed: A1.1, C5.2, L3.1
unnamed: C5.1, L4.1, U3.2 (LDA)
unnamed: C6.1, U3.28 (XTAL_IN), X1.1
unnamed: C7.1, U3.27 (XTAL_OUT), X1.2
unnamed: P4.3, U3.8 (XPD_DCDC)
unnamed: P4.4, U3.5 (VDD_RTC)
unnamed: P4.6, U3.6 (TOUT)
unnamed: P5.2, U3.15 (GPIO0)
unnamed: R2.2, U3.32 (EXT_RSTB)
unnamed: R3.2, U3.31 (RES12K)
unnamed: R4.1, U3.13 (MTDO)
unnamed: R5.1, U3.14 (GPIO2)
